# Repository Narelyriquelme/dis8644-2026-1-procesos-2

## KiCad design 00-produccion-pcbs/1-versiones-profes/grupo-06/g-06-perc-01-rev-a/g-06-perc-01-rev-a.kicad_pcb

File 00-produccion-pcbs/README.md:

# produccion-pcbs

jornada maratónica sábado 06 junio 2026

equipo docente toma todos los proyectos de kicad entregados el día anterior, de proyecto-02, y con eso edita, revisa, y envía a producción.

hay 6 grupos de trabajo con una temática en particular, cada grupo realizó 2 esquemáticos con sus respectivas placas, en varias versiones que subieron a la carpeta 00-proyecto-02.

a continuación los apuntes de las distintas revisiones hechas de estos proyectos, para prepararlos para su producción física.

en este repo creamos 3 carpetas:

- 0-versiones-estudiantes: archivos de kicad con las versiones más recientes de proyectos de estudiantes
- 1-versiones-profes: archivos de kicad con las versiones revisadas y realizadas por equipo docentes
- 2-archivos-produccion: gerbers de producción, etiquetados como revA.

## grupo-01: piezos

- benjaminalvarez21
- Anaysval
- chknngttts
- ryukivol
- nicolasvaldesgreve

## grupo-02: secuenciadores

- isidoraalvarez
- tomascatri
- dayanapanitrur
- Estrabismx
- angel-udp

### g-02-secu-01-v03

en esquemático:

- agregamos resistor de clock in a ground, para pulldown.
- agregamos resistor entre 4040 Q0 patita 9 y salida
- agregamos resistor a cada salida de jack switch.
- cambiamos huellas de transistores a versión inline_wide para que tengan más espacio
- agregados mounting hole faltantes

en pcb:

- actualizamos conectores jack a la huella de la biblioteca, para poder rutear bien los nuevos resistores y no perdernos.

### g-02-secu-02

en esquemático:

- agregamos también resistores de protección en entradas y salidas.
- agregados mounting hole faltantes

en pcb:

- actualizamos conectores jack a la huella de la biblioteca, para poder rutear bien los nuevos resistores y no perdernos.

## grupo-03: osciladores 1

- vanessagarciaM
- antoloch
- ccarlabelenn
- arielorozco024
- Narelyriquelme

## grupo-04: osciladores 2

- antokiaraa
- santiagocifuvelez
- paulafuentesm
- kristelagj
- catalinaoyanedel
- yairaruiz

## grupo-05: filtros

- antoniaamc
- Catabalboa
- sebastianguevaralarotta
- CatalinaJeria
- Luisaatoro9

## grupo-06: percusiones

- terroiblea
- martinaechavarria-stack
- Nicolas-Miranda1312
- paredesvania
- Coff4

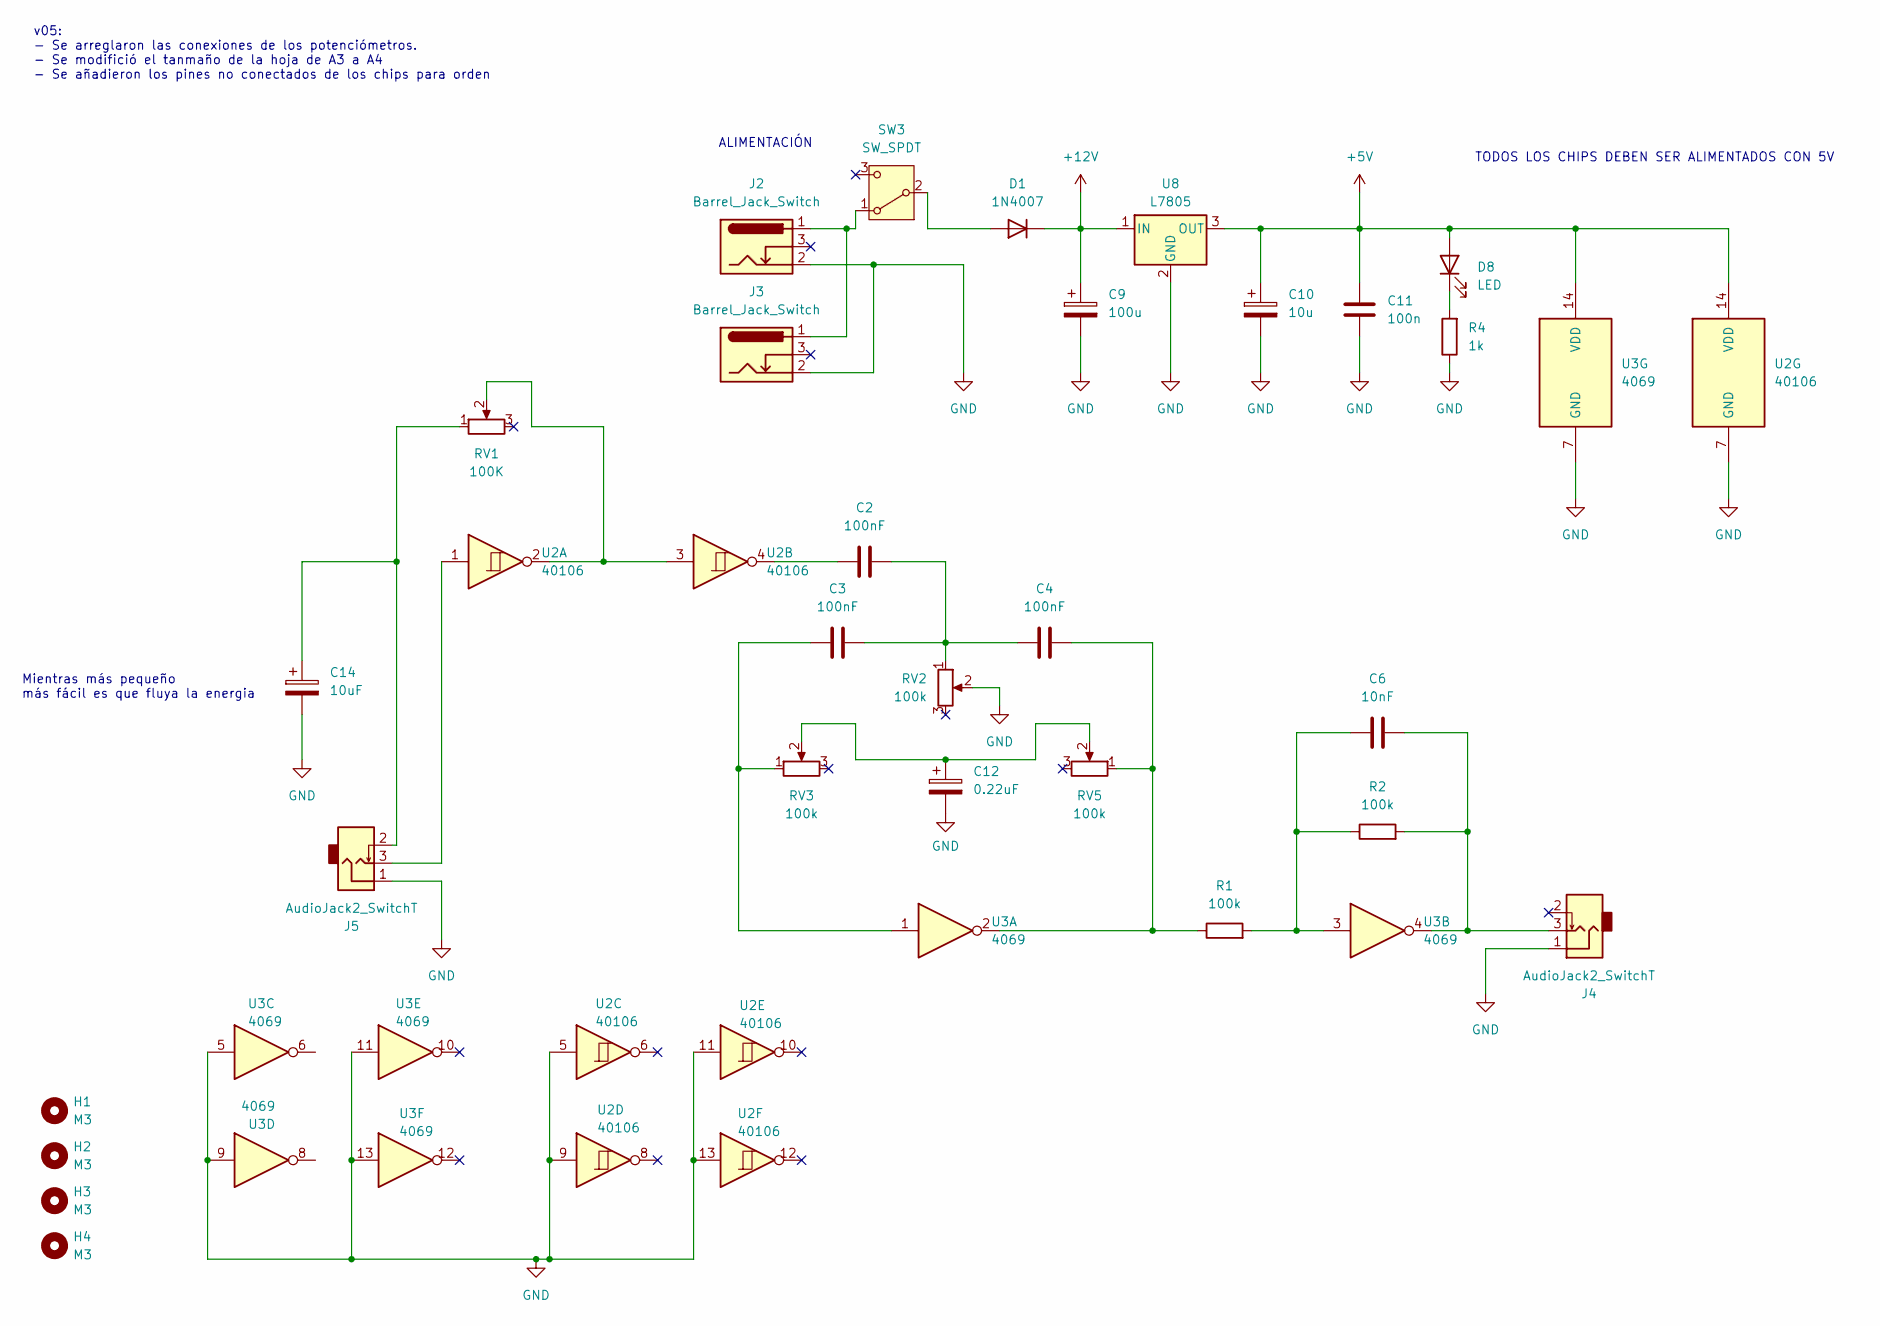
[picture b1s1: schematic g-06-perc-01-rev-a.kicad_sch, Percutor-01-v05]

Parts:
C2, C3, C4: 100nF; C_Disc_D3.8mm_W2.6mm_P2.50mm
C6: 10nF; C_Disc_D3.8mm_W2.6mm_P2.50mm
C9: 100u; CP_Radial_D8.0mm_P3.80mm
C10: 10u; CP_Radial_D4.0mm_P2.00mm
C11: 100n; C_Disc_D5.0mm_W2.5mm_P2.50mm
C12: 0.22uF; CP_Radial_D8.0mm_P3.80mm
C14: 10uF; CP_Radial_D8.0mm_P3.80mm
D1: 1N4007; D_DO-41_SOD81_P10.16mm_Horizontal
D8: LED; LED_D5.0mm
H1, H2, H3, H4: M3; MountingHole_3.2mm_M3
J2, J3: Barrel_Jack_Switch; BarrelJack_Horizontal
J4, J5: AudioJack2_SwitchT; PJ301M-12
R1, R2: 100k; R_Axial_DIN0207_L6.3mm_D2.5mm_P10.16mm_Horizontal
R4: 1k; R_Axial_DIN0207_L6.3mm_D2.5mm_P10.16mm_Horizontal
RV1: 100K; Potentiometer_Alps_RK163_Single_Horizontal
RV2, RV3, RV5: 100k; Potentiometer_Alps_RK163_Single_Horizontal
SW3: SW_SPDT; spdt_ssd12d00g3
U2: 40106; DIP-14_W7.62mm_LongPads
U3: 4069; DIP-14_W7.62mm_LongPads
U8: L7805; TO-220-3_Horizontal_TabDown

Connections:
+5V: C10.1, C11.1, D8.2 (A), U2.14 (VDD), U3.14 (VDD), U8.3 (OUT)
+12V: C9.1, D1.1 (K), U8.1 (IN)
GND: C9.2, C10.2, C11.2, C12.2, C14.2, J2.2, J3.2, J4.1, J5.1, R4.1, RV2.2, U2.5, U2.7 (GND), U2.9, U2.11, U2.13, U3.5, U3.7 (GND), U3.9, U3.11, U3.13, U8.2 (GND)
unnamed: C2.1, U2.4
unnamed: C2.2, C3.2, C4.1, RV2.1
unnamed: C3.1, RV3.1, U3.1
unnamed: C4.2, R1.1, RV5.1, U3.2
unnamed: C6.1, R1.2, R2.1, U3.3
unnamed: C6.2, J4.3, R2.2, U3.4
unnamed: C12.1, RV3.2, RV5.2
unnamed: C14.1, J5.2, RV1.1
unnamed: D1.2 (A), SW3.2 (B)
unnamed: D8.1 (K), R4.2
unnamed: J5.3, U2.1
unnamed: RV1.2, U2.2, U2.3
unnamed: J2.1, J3.1, SW3.1 (A)

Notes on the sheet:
TODOS LOS CHIPS DEBEN SER ALIMENTADOS CON 5V
ALIMENTACIÓN
v05: - Se arreglaron las conexiones de los potenciómetros. - Se modifició el tanmaño de la hoja de A3 a A4 - Se añadieron los pines no conectados de los chips para orden
Mientras más pequeño más fácil es que fluya la energia

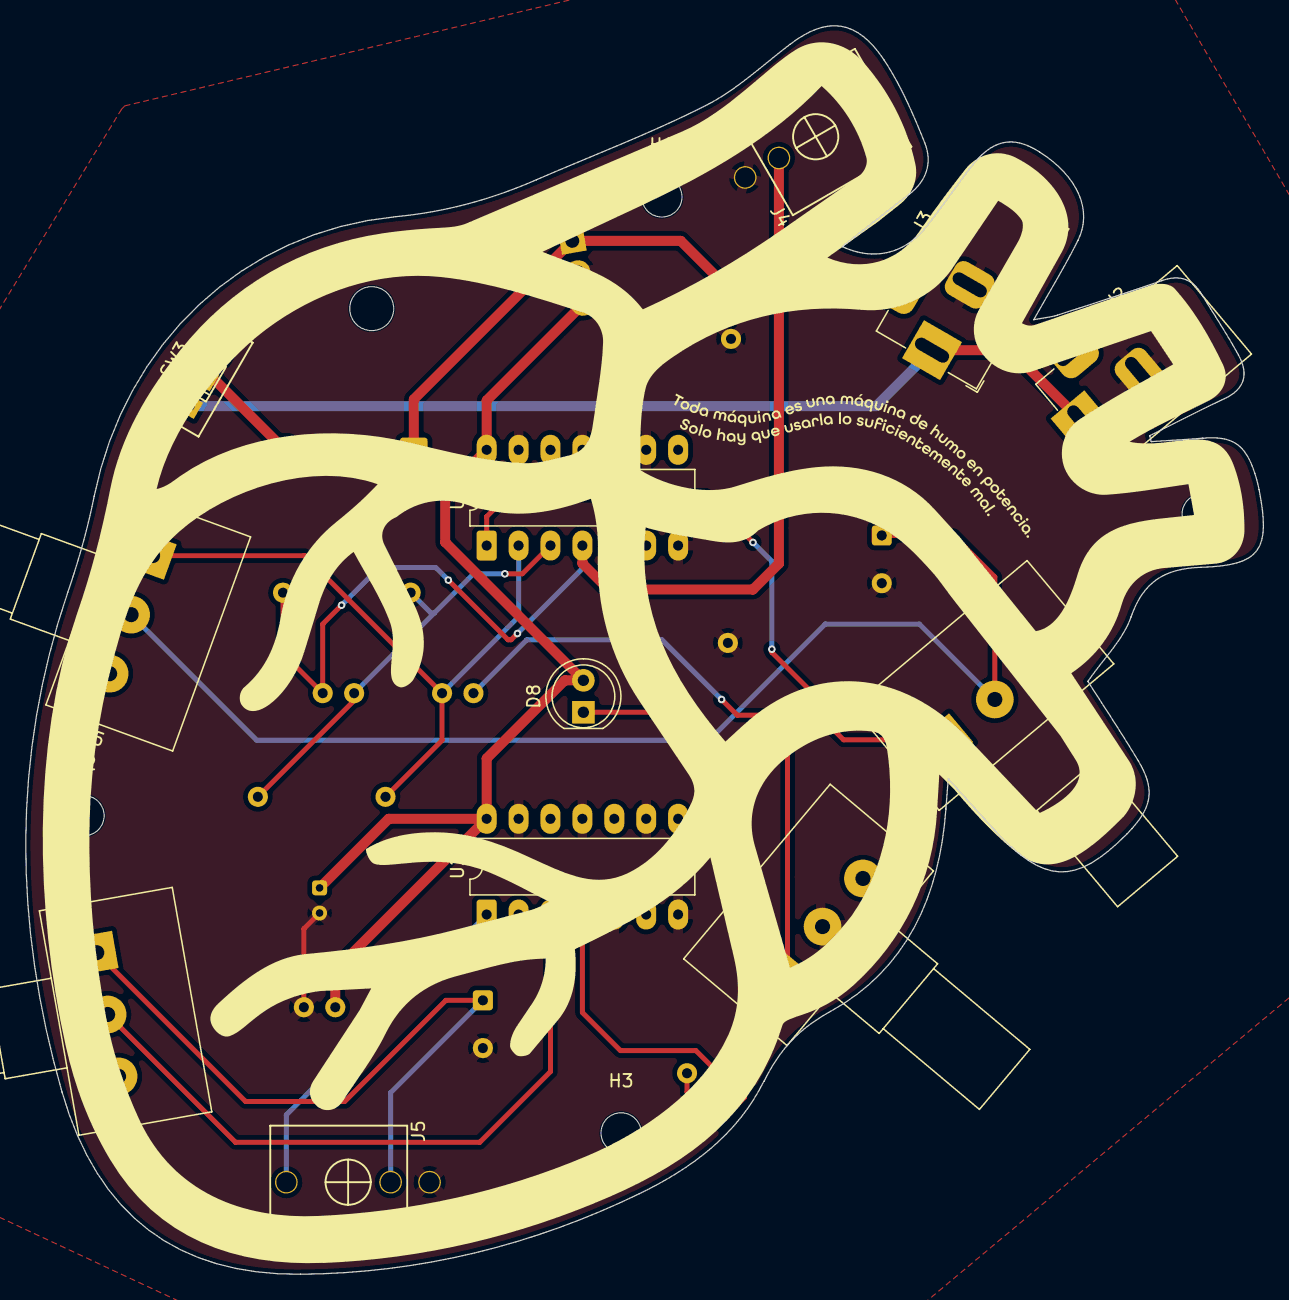
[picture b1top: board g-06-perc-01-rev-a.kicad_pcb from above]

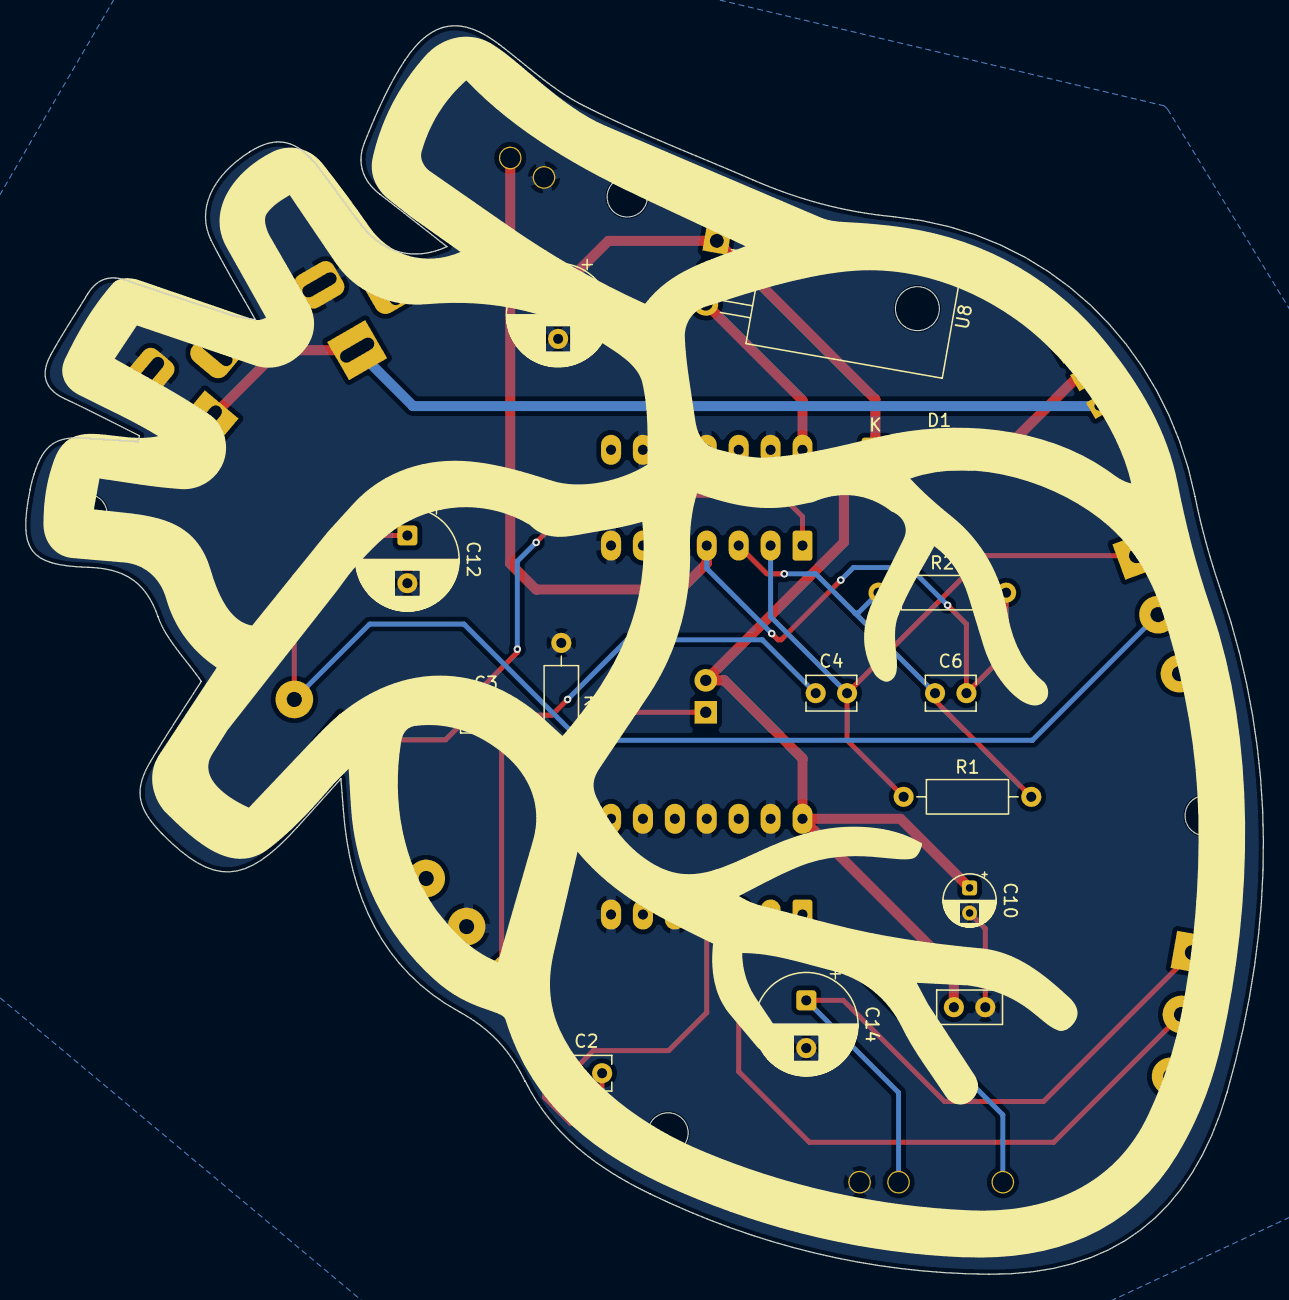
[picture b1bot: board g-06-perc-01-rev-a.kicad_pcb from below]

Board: 2 copper layers, 98.5 x 99.4 mm, 30 parts (14 on the bottom side), 16 nets.

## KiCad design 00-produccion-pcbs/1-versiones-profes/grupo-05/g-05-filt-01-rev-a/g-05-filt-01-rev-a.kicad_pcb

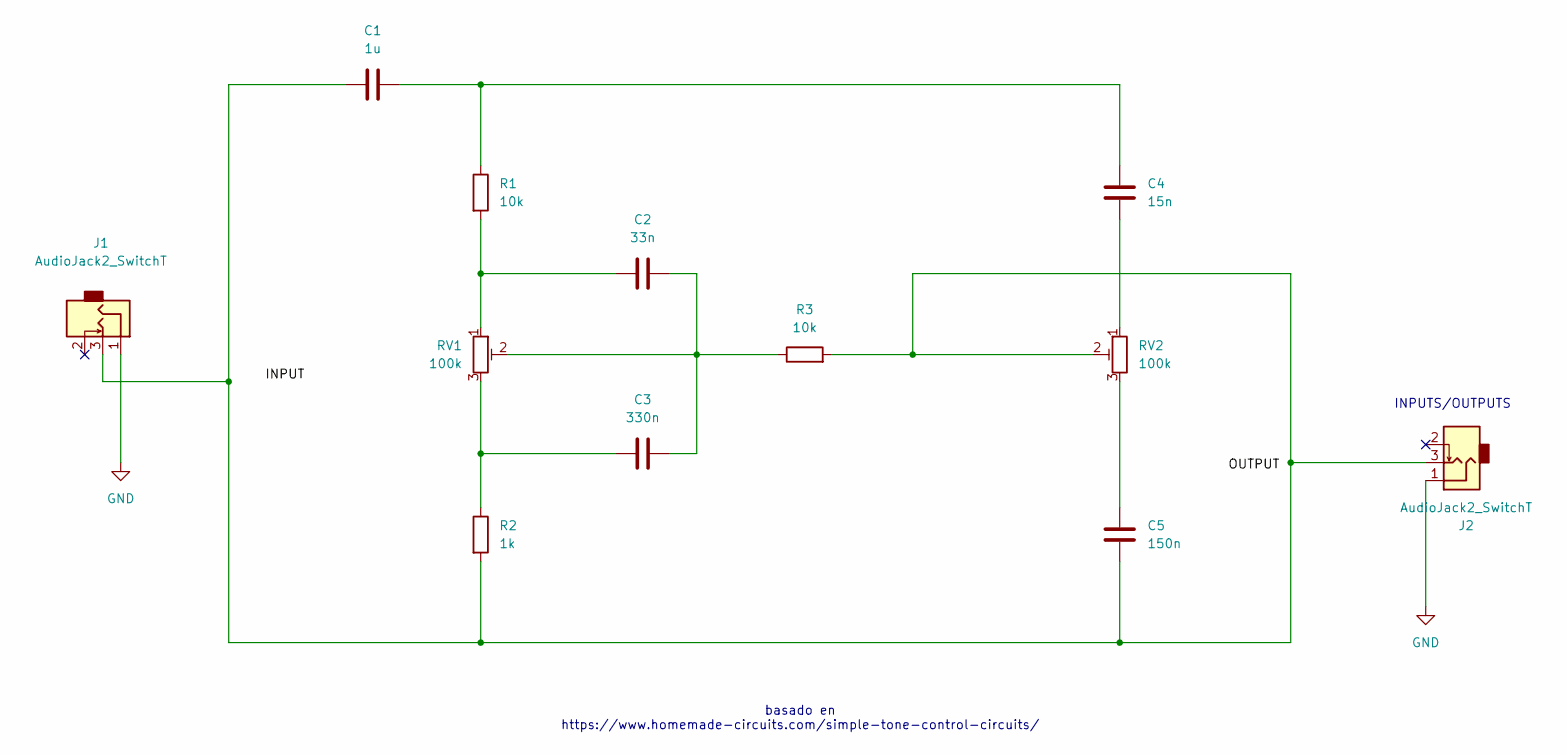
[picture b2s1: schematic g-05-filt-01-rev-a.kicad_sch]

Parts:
C1: 1u; C_Disc_D10.5mm_W5.0mm_P7.50mm
C2: 33n; C_Disc_D10.5mm_W5.0mm_P7.50mm
C3: 330n; C_Disc_D7.5mm_W5.0mm_P10.00mm
C4: 15n; C_Disc_D6.0mm_W2.5mm_P5.00mm
C5: 150n; C_Disc_D7.5mm_W4.4mm_P5.00mm
J1, J2: AudioJack2_SwitchT; PJ301M-12
R1, R3: 10k; R_Axial_DIN0207_L6.3mm_D2.5mm_P2.54mm_Vertical
R2: 1k; R_Axial_DIN0207_L6.3mm_D2.5mm_P2.54mm_Vertical
RV1, RV2: 100k; Potentiometer_Bourns_PTV09A-1_Single_Vertical

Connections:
GND: J1.1, J2.1
unnamed: C1.1, C5.2, J1.3, J2.3, R2.2, R3.2, RV2.2
unnamed 2: C1.2, C4.1, R1.1; also elsewhere on the board
unnamed: C2.1, R1.2, RV1.1
unnamed: C2.2, C3.2, R3.1, RV1.2
unnamed: C3.1, R2.1, RV1.3
unnamed 6: C4.2, RV2.1; also elsewhere on the board
unnamed 7: C5.1, RV2.3; also elsewhere on the board

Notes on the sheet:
basado en https://www.homemade-circuits.com/simple-tone-control-circuits/
INPUTS/OUTPUTS

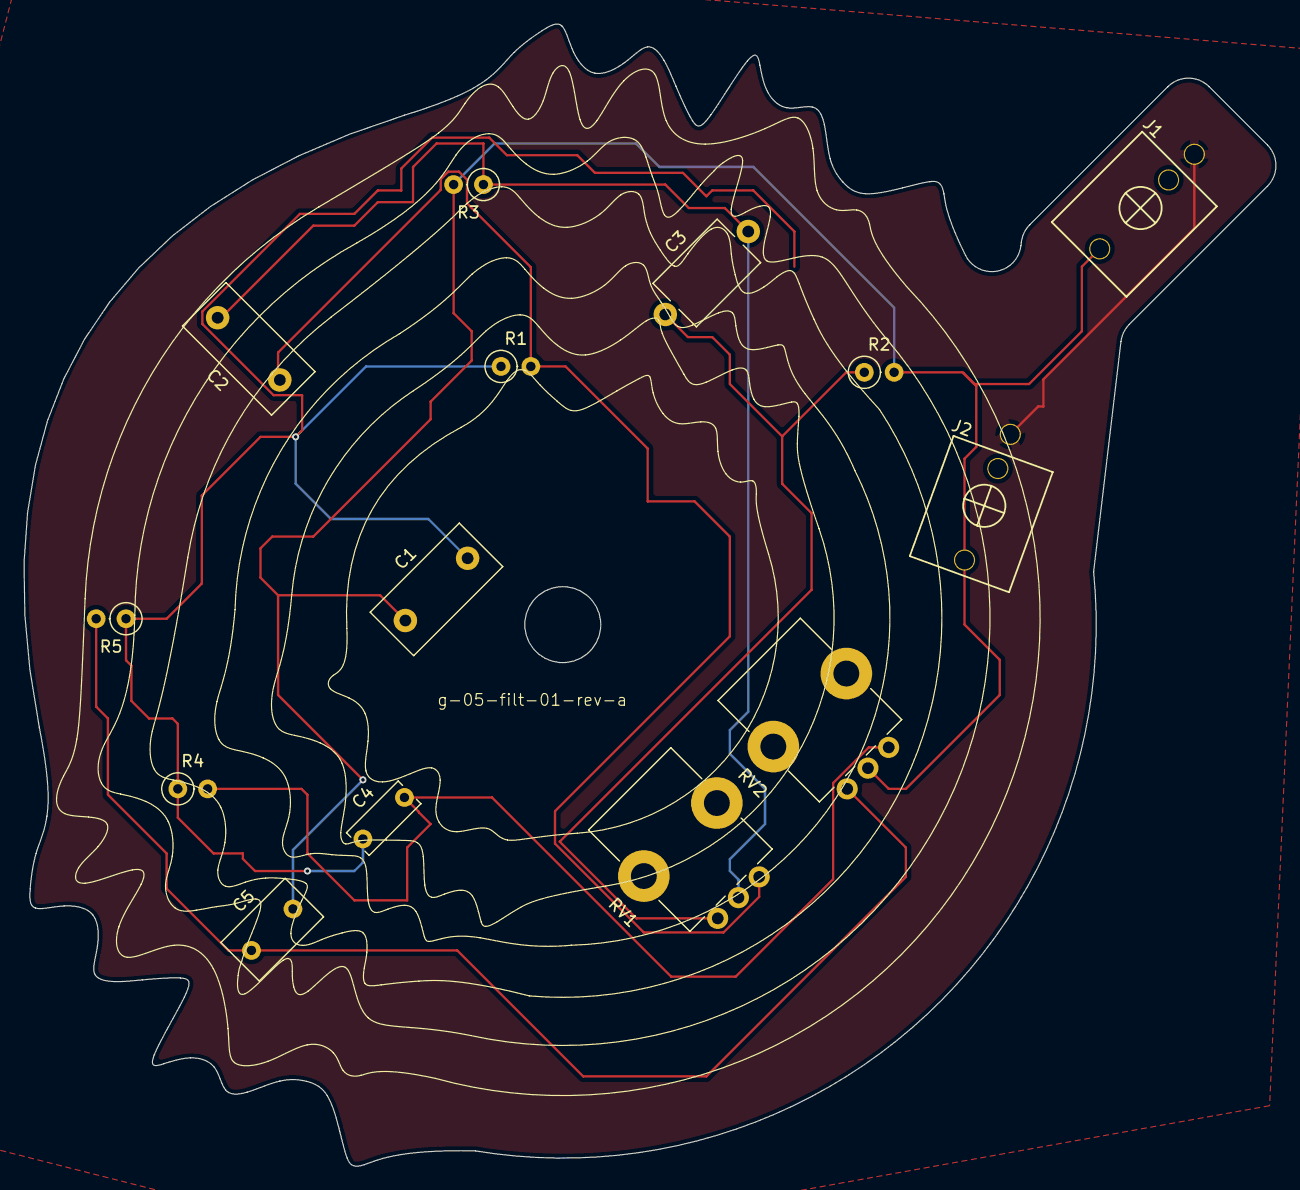
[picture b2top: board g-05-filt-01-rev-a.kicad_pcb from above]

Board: 2 copper layers, 106.7 x 97.3 mm, 14 parts (0 on the bottom side), 8 nets.

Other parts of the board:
R4: 10k; R_Axial_DIN0207_L6.3mm_D2.5mm_P2.54mm_Vertical
R5: 1k; R_Axial_DIN0207_L6.3mm_D2.5mm_P2.54mm_Vertical

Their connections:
unnamed 2: R4.1, R5.1; also elsewhere on the board
unnamed 6: R4.2; also elsewhere on the board
unnamed 7: R5.2; also elsewhere on the board

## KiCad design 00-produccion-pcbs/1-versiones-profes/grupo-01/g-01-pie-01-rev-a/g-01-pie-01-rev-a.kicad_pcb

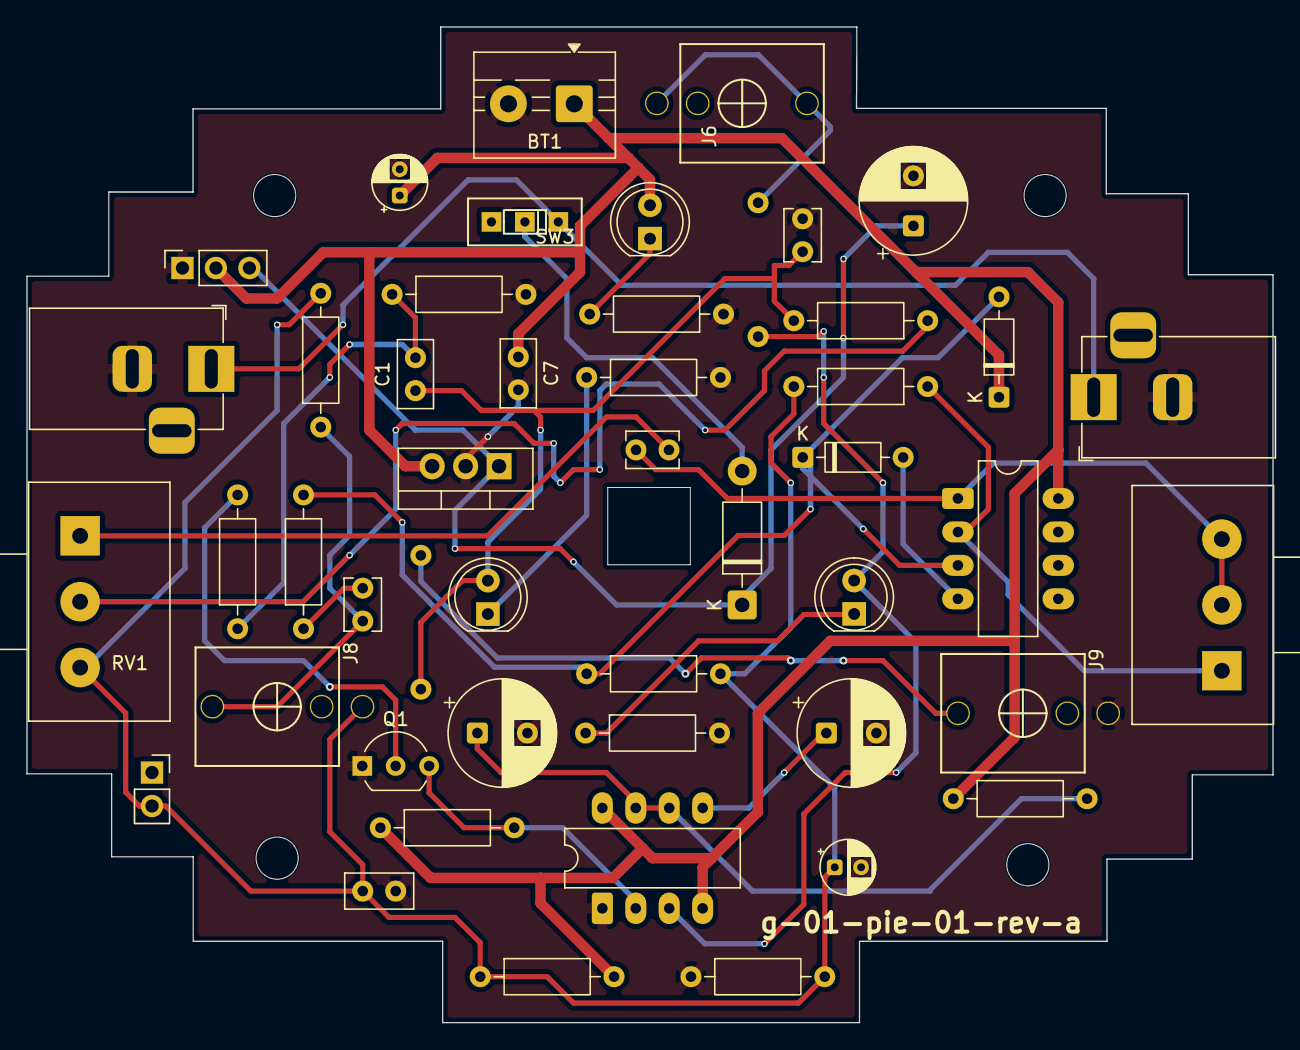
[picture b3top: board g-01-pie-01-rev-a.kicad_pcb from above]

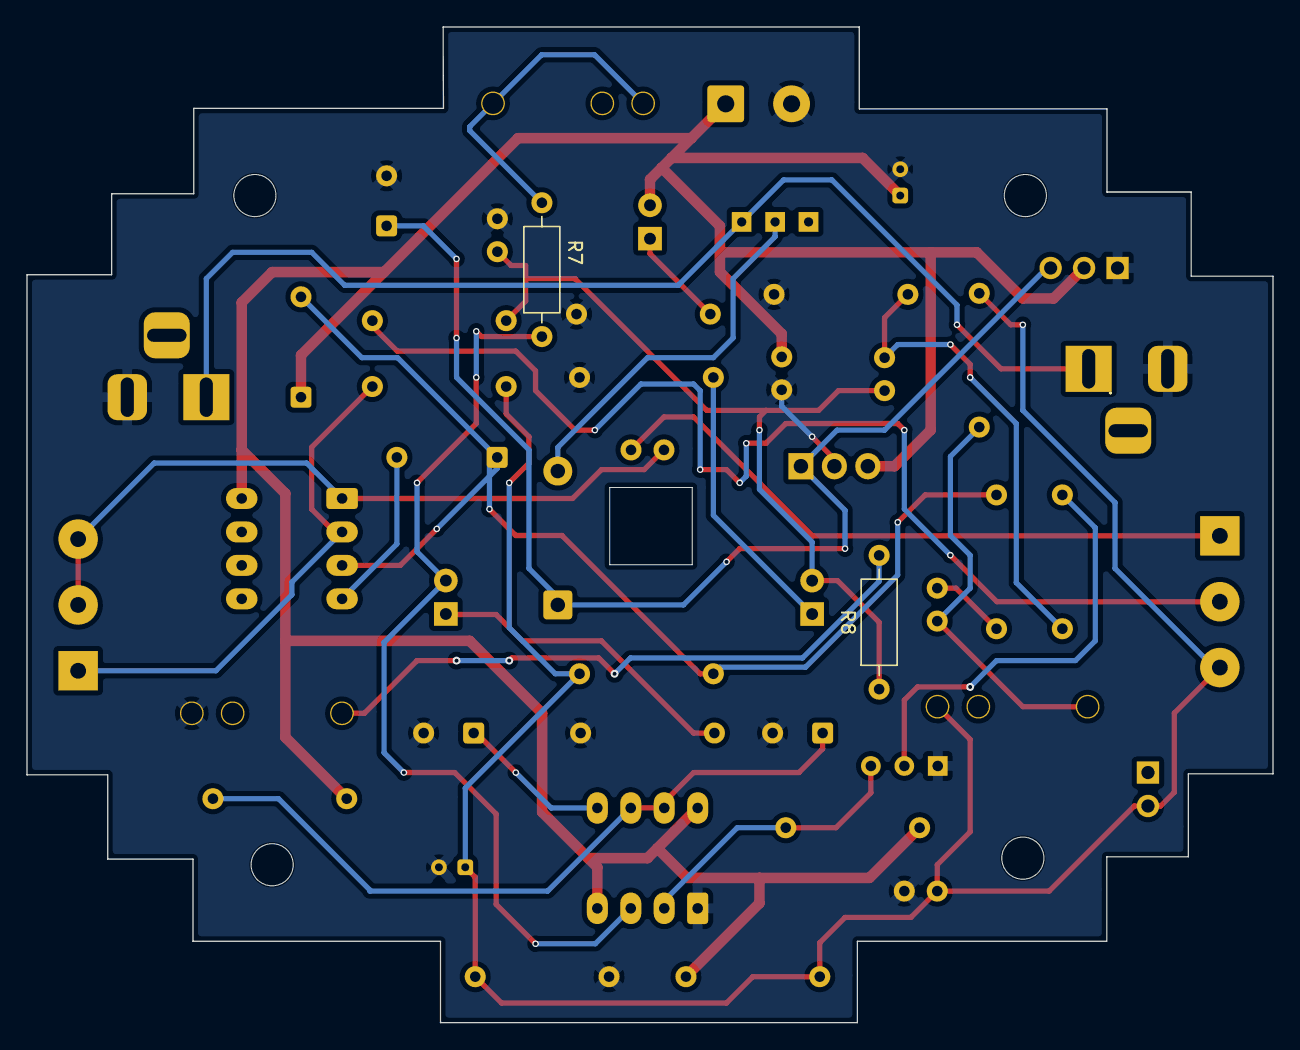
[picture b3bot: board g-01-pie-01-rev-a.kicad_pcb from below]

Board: 2 copper layers, 94.6 x 75.6 mm, 52 parts (2 on the bottom side), 26 nets.

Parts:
BT1: 5v; TerminalBlock_MaiXu_MX126-5.0-02P_1x02_P5.00mm
C1, C7, C10: 100n; C_Disc_D5.0mm_W2.5mm_P2.50mm
C2, C3, C5: 100u; CP_Radial_D8.0mm_P3.80mm
C6, C11: 10u; CP_Radial_D4.0mm_P2.00mm
C9: 1u; C_Disc_D3.8mm_W2.6mm_P2.50mm
C12: 4n7; C_Disc_D3.8mm_W2.6mm_P2.50mm
C13: 10n; C_Disc_D3.8mm_W2.6mm_P2.50mm
D1, D2, D8: LED; LED_D5.0mm
D5: 1N4007; D_DO-41_SOD81_P10.16mm_Horizontal
D6, D7: BAT85; D_DO-35_SOD27_P7.62mm_Horizontal
H1, H2, H3, H4: MountingHole; MountingHole_3.2mm_M3
J2: Conn_01x02_Pin; PinSocket_1x02_P2.54mm_Vertical
J4, J5: Barrel_Jack_Switch; BarrelJack_Horizontal
J6, J8, J9: AudioJack2_SwitchT; PJ301M-12
J7: Conn_01x03_Pin; PinSocket_1x03_P2.54mm_Vertical
Q1: 2N2222; TO-92_Inline_Wide
R1, R3, R6, R7, R8, R11: 1k; R_Axial_DIN0207_L6.3mm_D2.5mm_P10.16mm_Horizontal
R2, R16, R17: 100k; R_Axial_DIN0207_L6.3mm_D2.5mm_P10.16mm_Horizontal
R4, R5: 10k; R_Axial_DIN0207_L6.3mm_D2.5mm_P10.16mm_Horizontal
R12: 47; R_Axial_DIN0207_L6.3mm_D2.5mm_P10.16mm_Horizontal
R13: 2k; R_Axial_DIN0207_L6.3mm_D2.5mm_P10.16mm_Horizontal
R14: 220; R_Axial_DIN0207_L6.3mm_D2.5mm_P10.16mm_Horizontal
R15: 2M; R_Axial_DIN0207_L6.3mm_D2.5mm_P10.16mm_Horizontal
R18: 100; R_Axial_DIN0207_L6.3mm_D2.5mm_P10.16mm_Horizontal
RV1: B10k; Potentiometer_Alps_RK163_Single_Horizontal
RV2: B500k; Potentiometer_Alps_RK163_Single_Horizontal
SW3: SW_SPDT; spdt_ssd12d00g3
U1: NE555P; CERDIP-8_W7.62mm_SideBrazed_LongPads
U3: L7805; TO-220-3_Vertical
U4: TL072; CERDIP-8_W7.62mm_SideBrazed_LongPads

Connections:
+5V: BT1.1 (+), C6.1, C7.1, D6.1 (K), D8.2 (A), J7.2, R4.1, R5.1, R16.2, U1.4 (~RST), U1.8 (VCC), U3.3 (OUT), U4.8 (V+)
+12V: C5.1, D5.1 (K), J7.3, U3.1 (IN)
GND: BT1.2 (-), C2.2, C3.2, C5.2, C6.2, C7.2, C10.2, C11.2, C12.2, J4.2, J5.2, J7.1, J9.1, Q1.1 (E), R1.2, R2.2, R6.2, R11.1, R17.1, U1.1 (GND), U3.2 (GND)
unnamed: C1.2, R2.1, R3.1
unnamed: C9.1, J8.3, R15.1
unnamed: C9.2, R14.1
unnamed: C13.1, RV2.2, RV2.3, U4.1
unnamed: C13.2, RV1.1
unnamed: C1.1, C12.1, D1.2 (A), R8.1, R18.2
unnamed: D1.1 (K), R1.1
unnamed: D2.2 (A), R7.1, U1.3 (OUT)
unnamed: D2.1 (K), R6.1
unnamed: D5.2 (A), SW3.2 (B)
unnamed: D6.2 (A), D7.1 (K), R13.1, R14.2, U4.3 (+)
unnamed: D7.2 (A), U4.4 (V-)
unnamed: D8.1 (K), R11.2
unnamed: J6.1, J6.2, R7.2
unnamed: J9.3, R8.2
unnamed: Q1.2 (B), R3.2
unnamed: Q1.3 (C), R4.2, U1.2 (TRIG)
unnamed: R18.1, RV1.2
unnamed: J4.1, J5.1, SW3.1 (A)
unnamed: C3.1, U1.5 (CONT)
unnamed: C2.1, R5.2, U1.6 (THRES), U1.7 (DISCH)
unnamed: R12.1, RV2.1, U4.2 (-)
VBUS: C10.1, C11.1, J2.2, J8.1, R12.2, R13.2, R15.2, R16.1, R17.2, RV1.3

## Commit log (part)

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2026-05-14 Add section for encargo 09 in README.md
2026-05-17 Update README.md to reflect new session title
2026-05-17 Add 'feriadooooo' to README.md
2026-05-17 Add date and note to README for sesion-10a
2026-05-17 Add keyboard shortcut for adding a component
2026-05-18 Rename Captura de pantalla 2026-05-18 182931.png to encargo03.png
2026-05-19 Add holiday break note to README.md
2026-05-19 Update README with session notes and greetings
    Added a greeting and session details for KICAD.
2026-05-19 error-tamano
2026-05-19 tamano-correcto
2026-05-19 no-cambio-tamano-voy-denuevo
2026-05-19 agregar
2026-05-19 Update README.md to include image syntax
2026-05-19 Revise README.md with new section and details
    Updated section headers and added notes on voltage control and components.
2026-05-20 Se agrega analisis de capitulo 1 de bibliografia del curso.
2026-05-22 agrego imagen
2026-05-22 Update README with PCB visualization and challenges
    Added new images and detailed the 3D visualization process of the PCB, including challenges faced during component placement and routing. Discussed the importance of component compatibility and libra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
2026-05-22 Add date to README for sesion-10a
2026-05-22 sesion-in-correcta
2026-05-23 Trabajo en clases 10b
    Clarified description of KiCad schematic for clock and sequencer.
2026-05-25 agrego imagen pcb
2026-05-25 avance investigación
2026-05-26 Rename 00-proyecto-02/grupo-04/imagenes/Captura de pantalla 2026-05-26 105630.png to 00-proyecto-02/grupo-04/imagenes/![esquemático circuito](./imagenes/esquematico-1.png)
2026-05-26 ignorar *-backups
2026-05-27 README
2026-05-28 Change circuit image from JPEG to PNG
    Updated image format from JPEG to PNG for circuit diagram.
2026-05-29 Update README title with additional information
2026-05-29 apuntes-011b
2026-06-02 Update README.md with project details and references
2026-06-02 Update README with CD4015 assembly process
    Added detailed process and observations for the CD4015 circuit assembly.
2026-06-03 cambiar-carpeta
2026-06-03 agrego parte bom
2026-06-03 agregar a
2026-06-03 agregar borrador web
2026-06-03 agregar mas divs
2026-06-04 Fix image formatting in README.md
    Updated images in the README for schematics and PCBs.
2026-06-04 agregar v05
2026-06-04 eliminar archivo borrar
2026-06-05 arreglo redacción
2026-06-05 Revise PCB images and enhance acknowledgments section
    Updated PCB images and added credits for assistance received.
2026-06-05 Create borrar
2026-06-05 Create oscilador2-01-v01
2026-06-05 agrego esquematico
2026-06-05 Rename secuenciador-01-v02-placa3d.PNG to secuenciador-01-v02-placa3d.png
2026-06-05 arreglo-pcb
2026-06-06 agregar grupo-02
2026-06-06 mover
2026-06-06 preparar archivos g01
2026-06-06 agregar bla
2026-06-06 añadido g05
2026-06-06 añadido g06-01
2026-06-09 imagenes-entrega
2026-06-09 Update README with project requirements and tasks
2026-06-14 Refactor README.md for clarity and conciseness
    Se eliminaron repeticiones y se mejoró la redacción para mayor claridad en el README.
2026-06-14 Update README with project component details
    Added detailed descriptions of components used in the project, including CD4046, NE555P, CD4017, and CD40106, along with images.
2026-06-15 en edicion
2026-06-17 Update README.md with project 02 details
    Added project details and soldering process description.
2026-06-17 imagenes-hola-alguien-lee-esto-signo-de-pregunta
2026-06-17 me faltó un punto lol
2026-06-18 Update README.md with new image and text corrections
    Added an image and made grammatical corrections in the text.
2026-06-19 Create dddd
2026-06-19 Update README with session date and contents
2026-06-22 Update README with soldering session details
    Added detailed notes on soldering components for the projects Lup Dup, Barry Benson, and Chirigüe, including challenges faced and techniques used.
2026-06-22 sesion 14a
2026-06-23 agrego libro
2026-06-24 Expand README with partituras and project ideas
    Added detailed explanations about musical scores and group work on synthesizer development.
2026-06-30 agregar examen
